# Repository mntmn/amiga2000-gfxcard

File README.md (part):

# MNT VA2000, an Amiga 2000 Graphics Card (Zorro II/III)

_Update January 16th, 2017:_ The MNT VA2000 is now a finished product (credits go to Scarab Hardware for making this happen) that you can buy. I shipped the first batch of 100 cards on christmas 2016 and the second batch is now being made. 

You can still grab one: http://mntshop.bigcartel.com/product/mnt-va2000-amiga-graphics-card-zorro-ii-iii-batch-2-preorder

The latest firmware update and drivers are always available here: http://mntmn.com/va2000/

This repository contains my Kicad schematics and Xilinx ISE/Verilog files for my graphics card project. This is a work in progress, started in October 2015. The first 4 prototypes were assembled in Jan/Feb 2016 and had noise problems, so I started a redesign on Feb 13, 2016.

On Mar 27th, 2016, the redesign worked and I could load a 16 bit 565BGR coded raw image from floppy into the graphics card that displayed a 1280x720p resolution (75mhz pixelclock).

In April 2016, I managed to get Workbench running via a reverse engineered Picasso96 driver.

The working Xilinx project for the new target platform (Scarab miniSpartan 6+) is now in the z2-minispartan folder. The main source file is: https://github.com/mntmn/amiga2000-gfxcard/blob/master/z2-minispartan/z2.v

Contains a modified SDRAM controller (Verilog) and a DVI encoder (VHDL) by Mike Field. See credits and license at the end.

# How I decided to make a graphics card for my Amiga 2000

_TL;DR: I spent my free time over the course of 5 months to make two open source graphics card prototypes for the Amiga 2000. I will make a third, release version; details at the end._

Somewhere in the middle of 2015 I revived my old A500 and acquired again an A1200. Using the A1200, I learned C++ and the basics of web programming in the late 90s. I also used to play many fantastic Amiga games back in the day, made my first music in ProTracker and my first digital graphics in Deluxe Paint. Re-experiencing the old system that was once so ahead of its time again made me curious about Commodore's history – and especially about the later, big and ambitious Amiga models (A3000, A4000…). This coincided with Amiga's 30th anniversary. A lot of new interviews with the original team(s) popped up, including Dave Haynie, who was a main designer of the A2000 and the Zorro III Bus.

I checked eBay for the "big" Amigas I never had, expecting them to be cheap, but found out that these boxes had turned into valuable collector's items. At the same time, A2000s were (and still are) affordable, so I chose to get one and put a 68040 and a SCSI card in it. But the system couldn't realize it's full potential; in the 90s you could already get, for example, a "Picasso" graphics card that could do VGA (and higher) resolutions at 16 or 24bit color depth. Nowadays, these totally outdated cards are rare and sold for ridiculous prices. My A2000 was stuck with 640x256 PAL resolution, 64 colors (ignoring HAM) or headache-inducing interlaced modes. 

Because of my work with microcontrollers, writing an OS for Raspberry Pi (http://interim.mntmn.com/) and my interest in low-level computer architectures in general, I decided in October 2015 in a feat of madness: "I'll just make my own graphics card. How hard can it be?"

It turned out to be a very, very challenging project, but luckily I got much further than expected. On the way, I had to learn how to design a PCB and get it manufactured, how to work with SMD parts, how to program in Verilog and synthesize code for an FPGA, how SDRAM and DVI/HDMI work (or how to get them to do at least something). I also had to find out how to write a driver for the sadly closed/undocumented Picasso96 "retargetable" graphics stack for AmigaOS 3.

The Amiga is probably the last 32-bit personal computer that is fully understood, documented and hackable. Both its hardware and software contain many gems of engineering and design. I hope that one day, we can have a simple but powerful modern computer that is at the same time as hackable and friendly as the Amiga was.

## The "engine": FPGA and SDRAM

As a platform for my first attempt (ultimately a failure) I chose the Papilio Pro development board, which has a Xilinx Spartan 6 FPGA and a few megabytes of SDRAM connected to it. It also has two pin headers that break out some of the general purpose input/output pins of the Spartan. I thought, OK – I could use the RAM to store the image (a framebuffer), and run a loop that goes through all the columns and rows of the picture in the correct speed and just output the bytes from the RAM to R,G and B output lines. I did this before with little Atmel microcontrollers – "bit-banging" a VGA image directly from the CPU – so I knew it was possible. I just didn't know that SDRAM (synchronous dynamic RAM) was a lot more complex to use than the integrated SRAM (static RAM) of common microcontrollers. To access data in a dynamic ram, you have to open banks, rows, precharge, refresh, and take care of startup and access delays:

Source: http://www.alliancememory.com/pdf/dram/256m-as4c16m16s.pdf

Mike Field's open source SDRAM controller written in VHDL and Verilog helped me get the RAM working. I connected an Arduino to the Papilio and used it to send a few address bits and an "on/off" bit to toggle pixels in the framebuffer black or white. This contraption was able to draw basic fonts on my VGA display, and they were successfully kept in the SDRAM. 

The next step was connecting the FPGA+display part to the Amiga 2000.

## Zorro II: Reads and Writes

The original Amiga Hardware Manuals helped me understand the Zorro II bus. It is basically an extension (arbitrated by a bus controller chip) of the pins of the Motorola 68000 CPU. The 68k is extensively studied and documented. I understood that I needed a mechanism that would allow the 68k CPU to write data (pixels) to the graphics card's RAM and another for reading back parts of the screen (for scrolling and moving around things).

So I fired up the open source circuit design tool KiCad and started some schematics. The first task was to define the Zorro port as a component with a whopping 100 pins. Of course I made a lot of little mistakes at first and I had no idea why one would need so many different signals. It turned out that I only needed a subset of the pins to get my job done:

1. Address Bus (A1-A23)
2. Data Bus (D0-D15)
3. Upper and Lower "Data Strobes" (UDS / LDS)
4. READ, /AS, DOE, signals which the Amiga uses to communicate if it wants to read or write, if it presents a valid address and if it expects a device to send data.
5. Power (5V, GND)
6. Autoconf (/CFGIN, /CFGOUT)

Source: https://web.archive.org/web/20140513181907/http://courses.cs.tamu.edu/cpsc462/walker/Slides/68K_Timing_Diagrams.pdf

I figured that I needed to connect most of these signals to the FPGA and then write another loop in Verilog that would interpret the Amiga's bus commands and act on them (store the data given on the bus in the RAM or return stuff from the RAM). 

On the other side of the FPGA, I decided to place an Analog Devices ADV7125 digital to analog converter (DAC) chip that would generate the analog R, G and B channels for the VGA port from the bits coming from the framebuffer.

Source: http://www.analog.com/media/en/technical-documentation/data-sheets/ADV7125.pdf

The next hurdle appeared: The Spartan communicate with modern 3.3V logic levels, but the Amiga used legacy 5V signals. So I needed to put voltage translators (also called level shifters) between the Zorro and the FPGA pins. I decided to split the signals into bundles of 8 and use six 8-bit "auto-direction-sensing" TXS0108 chips.

Source: http://www.ti.com/lit/ds/symlink/txs0108e.pdf

## Mistake: Trying to be too smart

I then realized that the Papilio, the FPGA board I had, didn't have enough I/O pins to connect to the 48 Zorro signals and the 16+2 pins required for the VGA DAC output. Actually, it had a lot less pins. So I made a huge mistake and decided to use two 16-bit port switching chips and "select" on the fly a "window" of the Zorro pins that would be relevant at each state of my bus communication loop; I thought I didn't need to access the data pins at the same time as the address pins. And because the FPGA runs at a much higher frequency than the Zorro bus, I could first read one part of the address, switch one of the switches via a control pin and then quickly read the other part to get the whole address.

After drawing up a few versions of the schematics and collecting the fitting footprints for the components from various GitHub repositories, I imported them into KiCad's PCB design tool and started drawing the actual circuit board. I had no experience doing this, so I worked through tutorials or just looked at how other people were solving their board design problems. Finally, I uploaded the exported "Gerber" files to DirtyPCBs.com, ordered, waited 8 weeks and nothing happened. I made the mistake of choosing the AirMail option, which has no tracking, and the package was lost. After getting no support from DirtyPCB, I chose to try again, this time selecting the DHL option with tracking and finally got my first ever printed circuit boards in the mail around 10 days later! By now, it was the middle of January 2016.

In parallel, I ordered the required chips and parts from Mouser; luckily I had gotten most of the footprints right, except for one logic gate IC that turned out to be a mistake anyway. I got to work and tried to solder my first SMD ICs using my trusted ERSA iron. 

It turned out I had made a number of critical mistakes in designing the boards: all of the voltage translators' OE pins were tied to GND when they should have had 3.3V, so they required manual bending and patching of the OE leg (yellow cables in the picture). I accidentally switched 3.3V and GND pins on the FPGA carrier headers, so I needed to reroute them with wires on the back. Because I misinterpreted the Multiplexer IC's datasheet, I also planned for a negating logic IC on their SEL pins which was totaly wrong. In the end I had to solder bridges instead of placing the 74LS04. 

After fighting through all of these issues and burning through a few boards, I finally got some results. As a first debugging step, I wrote a poor man's logic analyzer in Verilog that would record 640 cycles of all the Zorro Bus signals to FPGA registers (BRAM) and dump them as colorful lines on the VGA screen. This turned out to be a helpful instrument. I wrote a very simple program in 68k assembler for the Amiga that would read – in an endless loop – a word from address $e80000 and write it to $dff180 (a background color register). I made a boot floppy that would run the program, put my card in the A2000, flashed the code and turned everything on.

The first 5 longer, stretched rows in this picture are the signals DOE, READ, /UDS, /AS and E7M (Amiga 7Mhz Clock) sampled at 100 Mhz/Column, so the whole picture displays a time sample of 6400ns (nanoseconds) or 6.4&mu;s (microseconds).

The following lines on the grid represent the Address bits A23-A1 in descending order. A0 does not exist; the 68000 selects an upper, lower or both bytes (word access) using /UDS and /LDS instead.

The address signals have regular little chops in them; this is a nasty side effect of switching the multiplexers. You can also see that address bit A9 is constantly turned on, probably due to a soldering error. At least it's possible to see the 68000's read and subsequent write accesses (the only hole in the READ row, second from the top). Ignoring the broken pins A9 and A17, the READ occurs as expected on address binary 111010000000000000000000 and the WRITE on 0b110111111111000110000000. Due to the constant noise and other random failures, I couldn't reliably get the Amiga to read from my card, but it worked at least sometimes, giving me hope.

After a few nights of trying to fix this very unstable system, I gave up and went back to the drawing board.

## Redesign and Breakthrough

My new strategy was:
1. Make the board much simpler, focus on voltage translation and find a FPGA board with enough IOs
2. Get a decent (de-)soldering station and learn a better SMD soldering technique

I shopped around the web for FPGA boards that combine SDRAM with lots of IO breakouts and found Scarab Hardware's miniSpartan6+, which has a nice small formfactor and includes two HDMI ports, a mini SD card reader and even an audio jack. 

I redrew the schematics to include no more switches, different level shifters with explicit direction inputs (NXP 74LVC8T245), plenty of bypass capacitors and dropped the analog VGA circuit. 

To solve point 2, I ordered a Yihua 853D rework station on Aliexpress and experimented with hot air solder paste soldering (not a success for me, the results were quite messy). I then watched Sparky's super helpful SMD soldering techniques again: https://www.youtube.com/watch?v=z7Tu8NXu5UA

To my surprise, using the "dragging" technique with plenty of flux and a chisel tip (Sparky recommends a "gullwing" tip) at around 270 Celsius yielded the cleanest results I had so far.

Version 2 rewarded me with super clean signals. I used 5 digital outputs of the FPGA and connected them to a VGA monitor for testing, and I could reliably "lock" my Verilog state machine to the Zorro READ cycles. 

I proceeded to write a little 68k assembler program that reads the Amiga's mouse X and Y registers and translates them into an address for the graphics card to write a pixel to. And voila, I had a primitive painting program:

The main problems I had to solve now revolved around tweaking the state machine so that it would arbitrate the single RAM port between fetching pixels for display on the screen – something that is almost constantly happening, only not during blanking periods – and Amiga reads and writes to and from the graphics RAM. I still haven't completely solved this challenge, but I've come far enough for the system to be somewhat usable. The current algorithm works like this:

### Fetching

Shortly before the beginning of each displayed row, start the pixel _fetching_ process. In this state, a line buffer is normally filled with pixels for that line from SDRAM as fast as possible (133 MHz clock).

### Displaying

The VGA/DVI output process reads the pixels to be displayed from this line buffer at the pixel clock frequency (60~75 MHz for a 1280x720 output). This means that the fetching process always needs to be at least as quick or quicker than the displaying process, or there will be glitches (doubling of the last line).

### Host Writes

When the host CPU wants to write to graphics RAM, we don't let it write directly to the SDRAM (because we're probably currently accessing it for fetches). Instead, we save the host's write address and data to a _write queue_. The queue is drained (processed) whenever the line fetching is done for a row and in blanking periods.

I tested the stability of writes by putting the "mon" tool (http://aminet.net/package/dev/moni/mon165) on a floppy together with a raw 16 bit image (rgb565) of a mountain. I loaded this directly into graphics card memory starting at $600000, displaying the first picture ever on my board:

### Host Reads

I found host read timing to be significantly harder to get right, and it's still not perfect. Host reads can't be put in a queue and have to be processed immediately. This interrupts the fetching process; if the host needs to read from a totally different memory location then the display engine is fetching, the SDRAM has to close, refresh and reopen rows, which is a time consuming process. So far, reads from the host cause temporary distortions (glitches) in the display output. I plan to mitigate these problems using either burst mode reads and fast switching and/or inserting CPU wait states via the XRDY signal.

## Picasso96: Writing a Driver for a Closed System

Picasso96 was one of two competing systems (the other being CyberGraphX) integrating graphics cards into the Amiga "Monitor" Device system. P96 also ships an "emulation.library" that patches all system windowing and drawing functions and redirect the legacy bit-planar based output to the new "chunky" pixel formats. After the death of Commodore and the Amiga market, Village Tronic, the authors of P96, disappeared. It's unclear where the sources and internal documentation ended up, and the original developers didn't respond to my emails about it.

I looked at the publically available P96 binaries and documentation and figured that I would need to write a _.card_ file, which is basically a normal Amiga library executable with a different file name extension. From inspecting the binaries and the UAE Picasso96 module, I figured out that my library would have to export a number of function symbols:

- FindCard() to detect if the board is available. I cheated and returned -1 (card found) in d0.
- InitCard(), the most important function, has the job of initializing the board and to fill in a "BoardInfo" structure with details like available pixel color formats, board type, horizontal and vertical maximum resolutions and timings (See: https://github.com/tonioni/WinUAE/blob/master/picasso96.cpp#L1082). This function also stores the addresses of the following callback functions into the BoardInfo structure.

- CalculateBytesPerRow() – Has to return the offset in bytes from one row of pixels to the next. For example: 2048 for a 1024 pixel wide 16-bit display.
- CalculateMemory() – Should remap an address in a1 to another (internal?) address. I just return a1 in d0.
- SetColorArray() – Set the palette for 256 color indexed CLUT mode. I didn't implement this yet.
- ResolvePixelClock() – Supposed to return an index into an array of pixel clocks. Return 0.
- GetPixelClock() – Given an index, return a pixel clock. I just return a fixed number of 60000000.
- SetPanning() – Called when a new P96 screen is opened. In the UAE code, they use it for screen clearing.
- SetSpriteColor() – Just return 0.
- SetDisplay() – enable/disable the display. Just return 0.
- WaitVerticalSync() – Just return 1 or actually sync to the screen refresh process.

Unknown functions: (Stubs that can return 1/0)
- SetSwitch() – Something related to switching between native Amiga and Picasso96 screens.
- SetDAC()
- SetClock()
- GetCompatibleFormats()
- GetVSyncState()
- SetMemoryMode()
- SetWriteMask()
- SetReadPlane()
- SetClearMask()

There is also a number of entrypoints to allow hardware blitting (block copying), rectangle fills and line drawing. I don't implement these yet, but they should speed up working with the card significantly. 

To activate my driver, I had to change the Picasso96 monitor file's "BoardType" tooltype to "VA2000". And indeed, it loaded my VA2000.card without complaining. I then launched the Picasso96Mode application that allows (somewhat erratically) to edit and enable/disable screen modes. To get it to do anything, I copied by trial and error the supplied Picasso96Settings.64 to DEVS:Picasso96Settings and attached the settings to my board that was now showing up in Picasso96Mode's "Board" menu. To my surprise, I could activate the 800x600 mode in "HiColor" and was greeted with a test image and then a somewhat distorted Workbench Screen:

Sprites such as the mouse pointer are emulated in software by Picasso96. In this image you can see some red noisy "turds" from where the mouse pointer was in the frames before – this shows that reading from card memory wasn't working right:

## Fixing the Colors

After playing around with Workbench and several applications, I noticed that somehow I could get only around 64 colors out of the 65535 that should be displayed. This turned out to be a problem of the color format. Picasso96 supports a bunch of 16 bit color modes; for some reasons I had used a "PC" mode (gggrrrrrbbbbbggg) which results in a weird truncation of the color space.

By changing the list of supported color modes in my driver to a non-PC-mode (RGB565), I was able to fix the problem and enjoy "High Color" in 800x600 on my Amiga 2000:

UniView displaying a JPEG (from Hood By Air show):

Obligatory shot of Doom:

## TODO

I will make one more version of the card supporting a reliable manufacturer's FPGA board and the following improvements. If you have the knowledge / tips on how to tackle any of these, feel free to contact me or submit pull requests:

- Fix the remaining noise in writes/reads
- Wait states via XRDY signal: If READ timing cannot be guaranteed or the WRITE queue is full, the card could ask the host CPU to wait by asserting XRDY, avoiding loss of data.
- Switching resolutions and color modes including true color (24 bit)
- Basic hardware block copy and rect filling support
- Digitizing and scandoubling the native amiga video for HDMI output
- Design a proper metal slot plate for connectors

## How can I build or buy a VA2000 board?

I still have to finish the "release" version of the board including the above fixes. I plan to offer preassembled versions and/or construction kits at reasonable prices. If you want to reserve a board, please send me an email to lukas@mntmn.com including "VA2000" in the subject.

All aspects of the project (schematics, PCB, verilog, driver sources) are or will be published as open source under the MIT license, so you are free to produce your own clones of the board.

## Sources, References, Thanks

Special thanks to Martin Åberg for sharing his "GRETA" Amiga 500 expansion sources (https://github.com/endofexclusive/greta). It inspired me to include bus signal synchronizers and helped with AUTOCONF.

Special thanks to Mike Field, his SDRAM and HDMI sources saved me a lot of time:
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
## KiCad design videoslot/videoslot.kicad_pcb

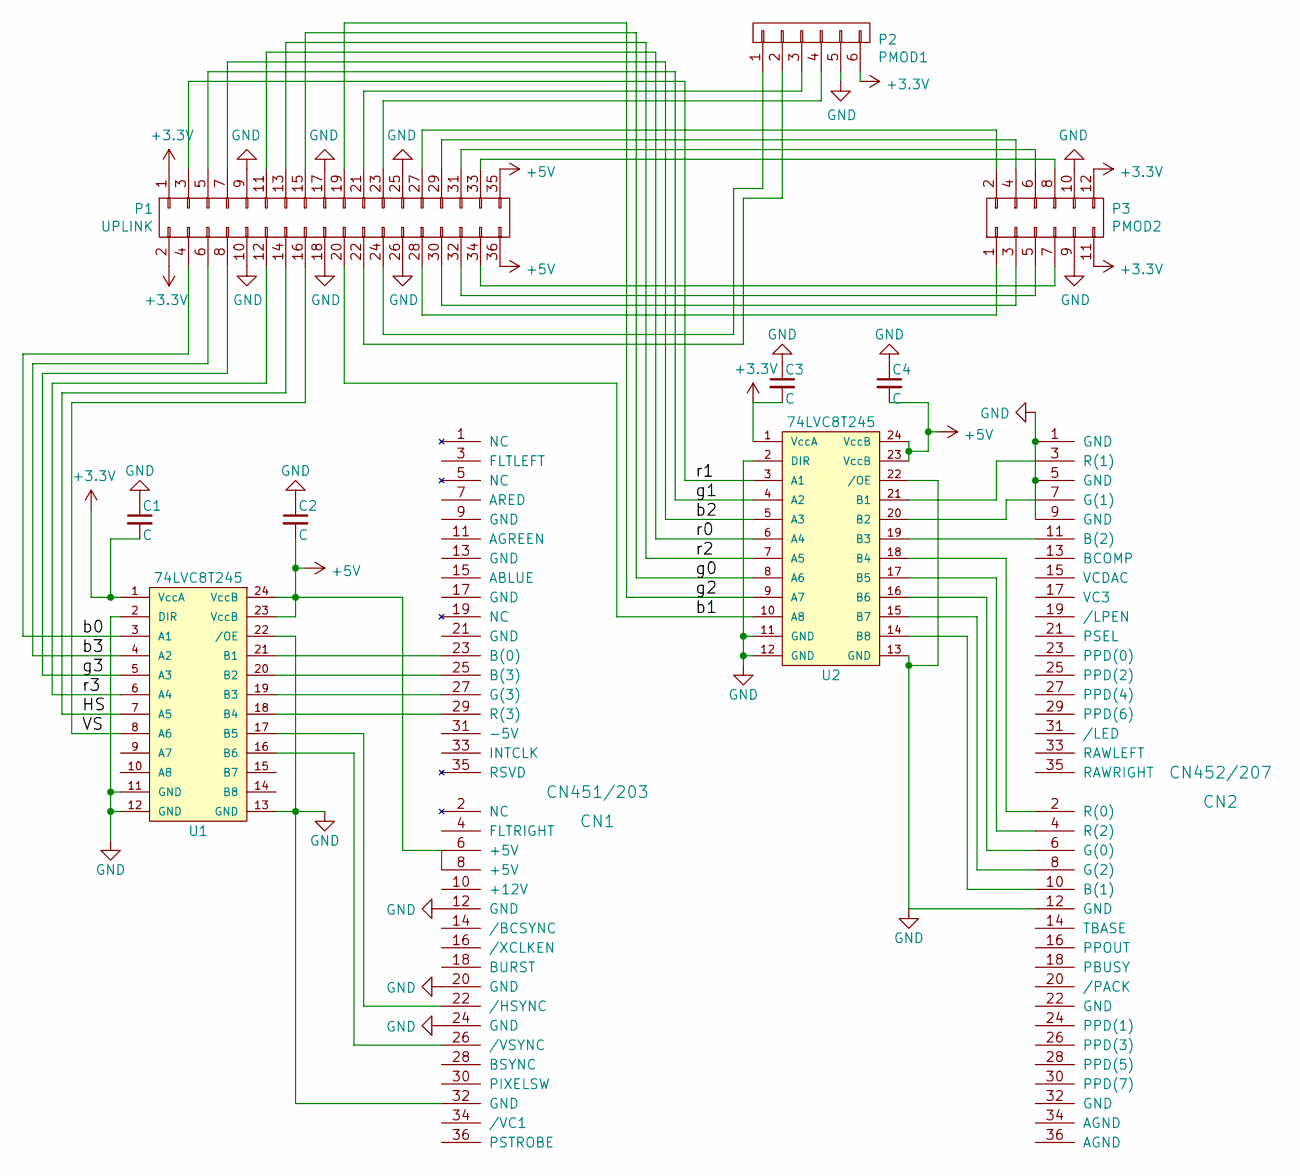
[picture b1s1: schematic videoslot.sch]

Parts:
C1, C2, C3, C4: C; C_0805_HandSoldering
CN1: CN451/203; CN451
CN2: CN452/207; CN452
P1: UPLINK; Pin_Header_Straight_2x18_Pitch2.54mm
P2: PMOD1; Pin_Header_Angled_1x06_Pitch2.54mm
P3: PMOD2; Pin_Header_Angled_2x06_Pitch2.54mm
U1, U2: 74LVC8T245; TSSOP24-44

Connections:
+3V3: C1.2, C3.2, P1.1, P1.2, P2.6, P3.11, P3.12, U1.1 (VccA), U2.1 (VccA)
+5V: C2.2, C4.2, CN1.6 (+5V), CN1.8 (+5V), P1.35, P1.36, U1.23 (VccB), U1.24 (VccB), U2.23 (VccB), U2.24 (VccB)
/HS: P1.14, U1.7 (A5)
/VS: P1.16, U1.8 (A6)
/b0: P1.4, U1.3 (A1)
/b1: P1.20, U2.10 (A8)
/b2: P1.7, U2.5 (A3)
/b3: P1.6, U1.4 (A2)
/g0: P1.15, U2.8 (A6)
/g1: P1.5, U2.4 (A2)
/g2: P1.19, U2.9 (A7)
/g3: P1.8, U1.5 (A3)
/r0: P1.11, U2.6 (A4)
/r1: P1.3, U2.3 (A1)
/r2: P1.13, U2.7 (A5)
/r3: P1.12, U1.6 (A4)
GND: C1.1, C2.1, C3.1, C4.1, CN1.12 (GND), CN1.20 (GND), CN1.24 (GND), CN1.32 (GND), CN2.1 (GND), CN2.5 (GND), CN2.9 (GND), CN2.12 (GND), P1.9, P1.10, P1.17, P1.18, P1.25, P1.26, P2.5, P3.9, P3.10, U1.2 (DIR), U1.11 (GND), U1.12 (GND), U1.13 (GND), U1.22 (/OE), U2.2 (DIR), U2.11 (GND), U2.12 (GND), U2.13 (GND), U2.22 (/OE)
unnamed: CN1.22 (/HSYNC), U1.17 (B5)
unnamed: CN1.23 (B(0)), U1.21 (B1)
unnamed: CN1.25 (B(3)), U1.20 (B2)
unnamed: CN1.26 (/VSYNC), U1.16 (B6)
unnamed: CN1.27 (G(3)), U1.19 (B3)
unnamed: CN1.29 (R(3)), U1.18 (B4)
unnamed: CN2.2 (R(0)), U2.18 (B4)
unnamed: CN2.3 (R(1)), U2.21 (B1)
unnamed: CN2.4 (R(2)), U2.17 (B5)
unnamed: CN2.6 (G(0)), U2.16 (B6)
unnamed: CN2.7 (G(1)), U2.20 (B2)
unnamed: CN2.8 (G(2)), U2.15 (B7)
unnamed: CN2.10 (B(1)), U2.14 (B8)
unnamed: CN2.11 (B(2)), U2.19 (B3)
unnamed: P1.21, P2.3
unnamed: P1.22, P2.2
unnamed: P1.23, P2.4
unnamed: P1.24, P2.1
unnamed: P1.27, P3.2
unnamed: P1.28, P3.1
unnamed: P1.29, P3.4
unnamed: P1.30, P3.3
unnamed: P1.31, P3.6
unnamed: P1.32, P3.5
unnamed: P1.33, P3.8
unnamed: P1.34, P3.7

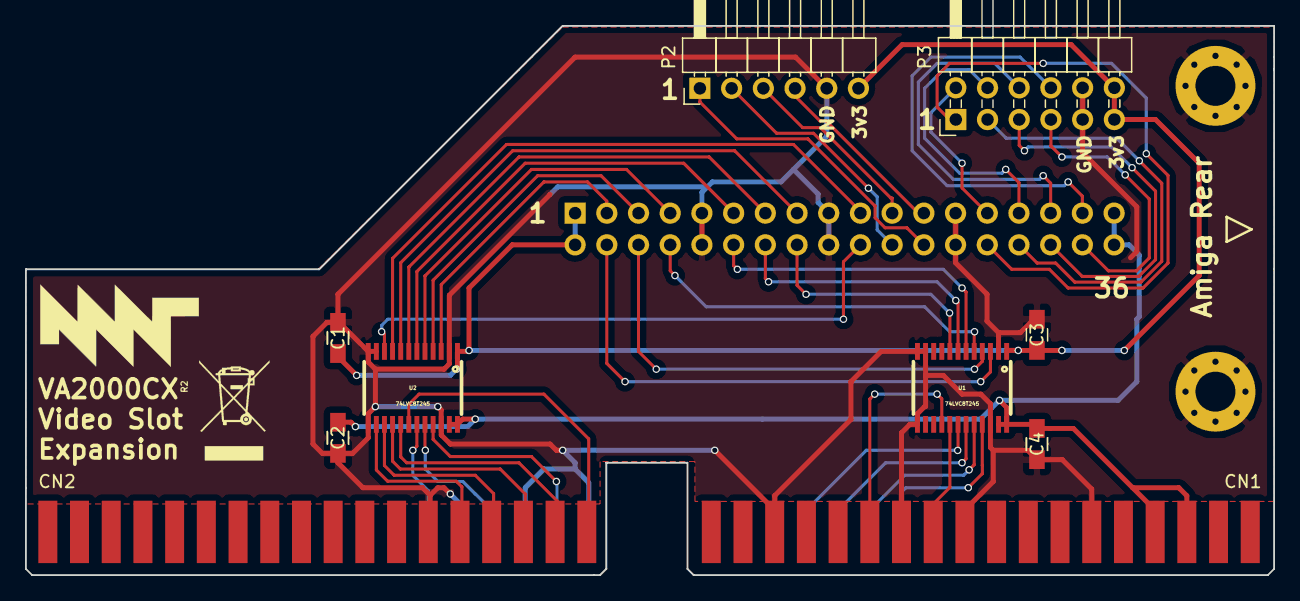
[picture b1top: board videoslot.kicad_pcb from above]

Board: 2 copper layers, 100.0 x 44.0 mm, 11 parts (1 on the bottom side), 43 nets.

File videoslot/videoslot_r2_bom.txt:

U1 U2: SN74LVC8T245PWR 8-Bit Dual-Supply Bus Xcvr
C1 C2 C3 C4: Murata GRM21BR71E104KA01L 0.1uF 0805
P1: Harwin M20-9960645 06 SIL HORIZONTAL PIN HEADER GOLD HT
P2: Harwin M20-9700645 06+06 DIL HORIZONTAL PIN HEADER GOLD HT
P3: Harwin M20-9981845 18+18 DIL VERTICAL PIN HEADER GOLD HT

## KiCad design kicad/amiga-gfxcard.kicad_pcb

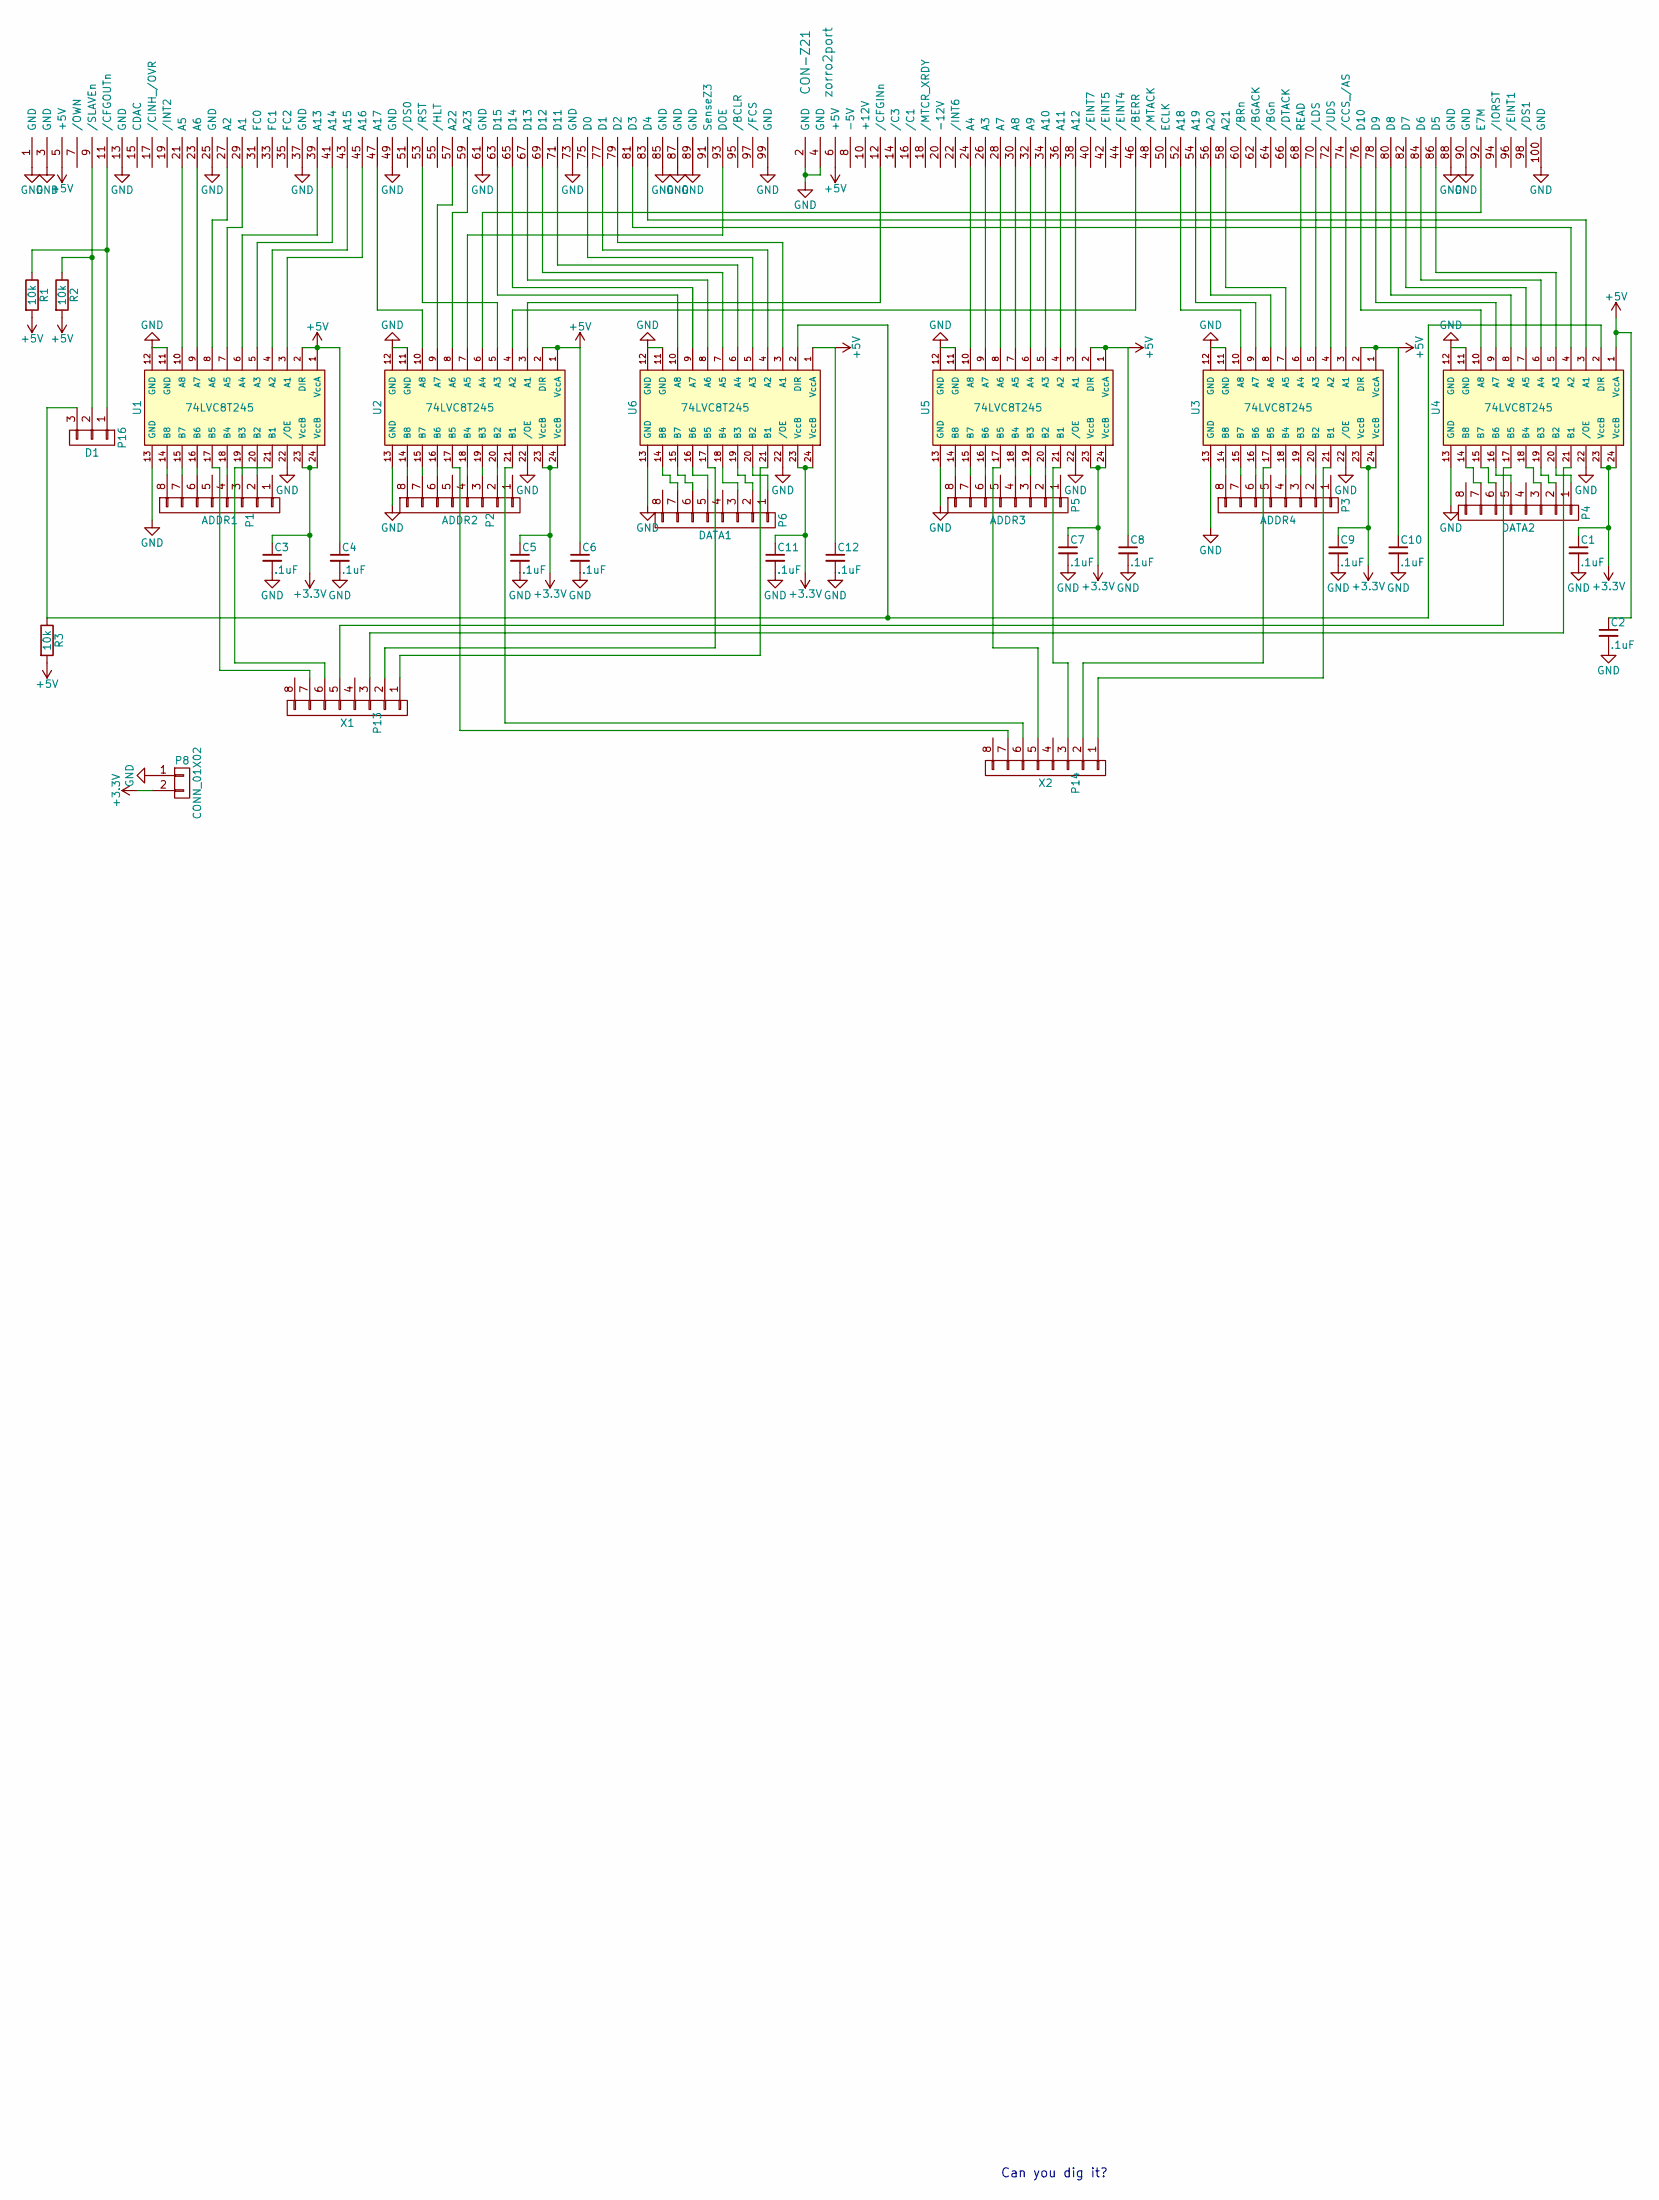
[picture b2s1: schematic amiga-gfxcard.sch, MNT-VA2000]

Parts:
C1, C2, C3, C4, C5, C6, C7, C8, C9, C10, C11, C12: .1uF; C_0805_HandSoldering
CON-Z21: zorro2port; zorro2card
P1: ADDR1; Pin_Header_Straight_1x08
P2: ADDR2; Pin_Header_Straight_1x08
P3: ADDR4; Pin_Header_Straight_1x08
P4: DATA2; Pin_Header_Straight_1x08
P5: ADDR3; Pin_Header_Straight_1x08
P6: DATA1; Pin_Header_Straight_1x08
P8: CONN_01X02; Pin_Header_Straight_1x02
P13: X1; Pin_Header_Straight_1x08
P14: X2; Pin_Header_Straight_1x08
P16: D1; Pin_Header_Straight_1x03
R1, R2, R3: 10k; R_1206_HandSoldering
U1, U2, U3, U4, U5, U6: 74LVC8T245; TSSOP24-44

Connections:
+3V3: C1.1, C3.1, C5.1, C7.1, C9.1, C11.1, P8.2, U1.23 (VccB), U1.24 (VccB), U2.23 (VccB), U2.24 (VccB), U3.23 (VccB), U3.24 (VccB), U4.23 (VccB), U4.24 (VccB), U5.23 (VccB), U5.24 (VccB), U6.23 (VccB), U6.24 (VccB)
+5V: C2.1, C4.1, C6.1, C8.1, C10.1, C12.1, CON-Z21.5 (+5V), CON-Z21.6 (+5V), R1.2, R2.2, R3.2, U1.1 (VccA), U1.2 (DIR), U2.1 (VccA), U2.2 (DIR), U3.1 (VccA), U3.2 (DIR), U4.1 (VccA), U5.1 (VccA), U5.2 (DIR), U6.1 (VccA)
GND: C1.2, C2.2, C3.2, C4.2, C5.2, C6.2, C7.2, C8.2, C9.2, C10.2, C11.2, C12.2, CON-Z21.1 (GND), CON-Z21.2 (GND), CON-Z21.3 (GND), CON-Z21.4 (GND), CON-Z21.13 (GND), CON-Z21.25 (GND), CON-Z21.37 (GND), CON-Z21.49 (GND), CON-Z21.61 (GND), CON-Z21.73 (GND), CON-Z21.85 (GND), CON-Z21.87 (GND), CON-Z21.88 (GND), CON-Z21.89 (GND), CON-Z21.90 (GND), CON-Z21.99 (GND), CON-Z21.100 (GND), P8.1, U1.11 (GND), U1.12 (GND), U1.13 (GND), U1.22 (/OE), U2.11 (GND), U2.12 (GND), U2.13 (GND), U2.22 (/OE), U3.11 (GND), U3.12 (GND), U3.13 (GND), U3.22 (/OE), U4.11 (GND), U4.12 (GND), U4.13 (GND), U4.22 (/OE), U5.11 (GND), U5.12 (GND), U5.13 (GND), U5.22 (/OE), U6.11 (GND), U6.12 (GND), U6.13 (GND), U6.22 (/OE)
unnamed: CON-Z21.9 (/SLAVEn), P16.2, R2.1
unnamed: CON-Z21.11 (/CFGOUTn), P16.1, R1.1
unnamed: CON-Z21.12 (/CFGINn), U2.3 (A1)
unnamed: CON-Z21.21 (A5), U1.10 (A8)
unnamed: CON-Z21.23 (A6), U1.9 (A7)
unnamed: CON-Z21.24 (A4), U5.10 (A8)
unnamed: CON-Z21.26 (A3), U5.9 (A7)
unnamed: CON-Z21.27 (A2), U1.8 (A6)
unnamed: CON-Z21.28 (A7), U5.8 (A6)
unnamed: CON-Z21.29 (A1), U1.7 (A5)
unnamed: CON-Z21.30 (A8), U5.7 (A5)
unnamed: CON-Z21.32 (A9), U5.6 (A4)
unnamed: CON-Z21.34 (A10), U5.5 (A3)
unnamed: CON-Z21.36 (A11), U5.4 (A2)
unnamed: CON-Z21.38 (A12), U5.3 (A1)
unnamed: CON-Z21.39 (A13), U1.6 (A4)
unnamed: CON-Z21.41 (A14), U1.5 (A3)
unnamed: CON-Z21.43 (A15), U1.4 (A2)
unnamed: CON-Z21.45 (A16), U1.3 (A1)
unnamed: CON-Z21.46 (/BERR), U2.4 (A2)
unnamed: CON-Z21.47 (A17), U2.10 (A8)
unnamed: CON-Z21.52 (A18), U3.10 (A8)
unnamed: CON-Z21.53 (/RST), U2.5 (A3)
unnamed: CON-Z21.54 (A19), U3.9 (A7)
unnamed: CON-Z21.56 (A20), U3.8 (A6)
unnamed: CON-Z21.57 (A22), U2.9 (A7)
unnamed: CON-Z21.58 (A21), U3.7 (A5)
unnamed: CON-Z21.59 (A23), U2.8 (A6)
unnamed: CON-Z21.63 (D15), U6.10 (A8)
unnamed: CON-Z21.65 (D14), U6.9 (A7)
unnamed: CON-Z21.67 (D13), U6.8 (A6)
unnamed: CON-Z21.68 (READ), U3.6 (A4)
unnamed: CON-Z21.69 (D12), U6.7 (A5)
unnamed: CON-Z21.70 (/LDS), U3.5 (A3)
unnamed: CON-Z21.71 (D11), U6.6 (A4)
unnamed: CON-Z21.72 (/UDS), U3.4 (A2)
unnamed: CON-Z21.74 (/CCS_/AS), U3.3 (A1)
unnamed: CON-Z21.75 (D0), U6.5 (A3)
unnamed: CON-Z21.76 (D10), U4.10 (A8)
unnamed: CON-Z21.77 (D1), U6.4 (A2)
unnamed: CON-Z21.78 (D9), U4.9 (A7)
unnamed: CON-Z21.79 (D2), U6.3 (A1)
unnamed: CON-Z21.80 (D8), U4.8 (A6)
unnamed: CON-Z21.81 (D3), U4.4 (A2)
unnamed: CON-Z21.82 (D7), U4.7 (A5)
unnamed: CON-Z21.83 (D4), U4.3 (A1)
unnamed: CON-Z21.84 (D6), U4.6 (A4)
unnamed: CON-Z21.86 (D5), U4.5 (A3)
unnamed: CON-Z21.92 (E7M), U2.6 (A4)
unnamed: CON-Z21.93 (DOE), U2.7 (A5)
unnamed: P1.2, U1.20 (B2)
unnamed: P1.3, U1.19 (B3)
unnamed: P1.4, U1.18 (B4)
unnamed: P1.6, U1.16 (B6)
unnamed: P1.7, U1.15 (B7)
unnamed: P1.8, U1.14 (B8)
unnamed: P2.2, U2.20 (B2)
unnamed: P2.3, U2.19 (B3)
unnamed: P2.4, U2.18 (B4)
unnamed: P2.6, U2.16 (B6)
unnamed: P2.7, U2.15 (B7)
unnamed: P2.8, U2.14 (B8)
unnamed: P3.2, U3.20 (B2)
unnamed: P3.3, U3.19 (B3)
unnamed: P3.4, U3.18 (B4)
unnamed: P3.6, U3.16 (B6)
unnamed: P3.7, U3.15 (B7)
unnamed: P3.8, U3.14 (B8)
unnamed: P4.1, U4.20 (B2)
unnamed: P4.2, U4.19 (B3)
unnamed: P4.3, U4.18 (B4)
unnamed: P4.5, U4.16 (B6)
unnamed: P4.6, U4.15 (B7)
unnamed: P4.7, U4.14 (B8)
unnamed: P5.2, U5.20 (B2)
unnamed: P5.3, U5.19 (B3)
unnamed: P5.4, U5.18 (B4)
unnamed: P5.6, U5.16 (B6)
unnamed: P5.7, U5.15 (B7)
unnamed: P5.8, U5.14 (B8)
unnamed: P6.1, U6.20 (B2)
unnamed: P6.2, U6.19 (B3)
unnamed: P6.3, U6.18 (B4)
unnamed: P6.5, U6.16 (B6)
unnamed: P6.6, U6.15 (B7)
unnamed: P6.7, U6.14 (B8)
unnamed: P13.1, U6.21 (B1)
unnamed: P13.2, U6.17 (B5)
unnamed: P13.3, U4.21 (B1)
unnamed: P13.5, U4.17 (B5)
unnamed: P13.6, U1.21 (B1)
unnamed: P13.7, U1.17 (B5)
unnamed: P14.1, U3.21 (B1)
unnamed: P14.2, U3.17 (B5)
unnamed: P14.3, U5.21 (B1)
unnamed: P14.5, U5.17 (B5)
unnamed: P14.6, U2.21 (B1)
unnamed: P14.7, U2.17 (B5)
unnamed: P16.3, R3.1, U4.2 (DIR), U6.2 (DIR)

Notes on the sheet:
Can you dig it?

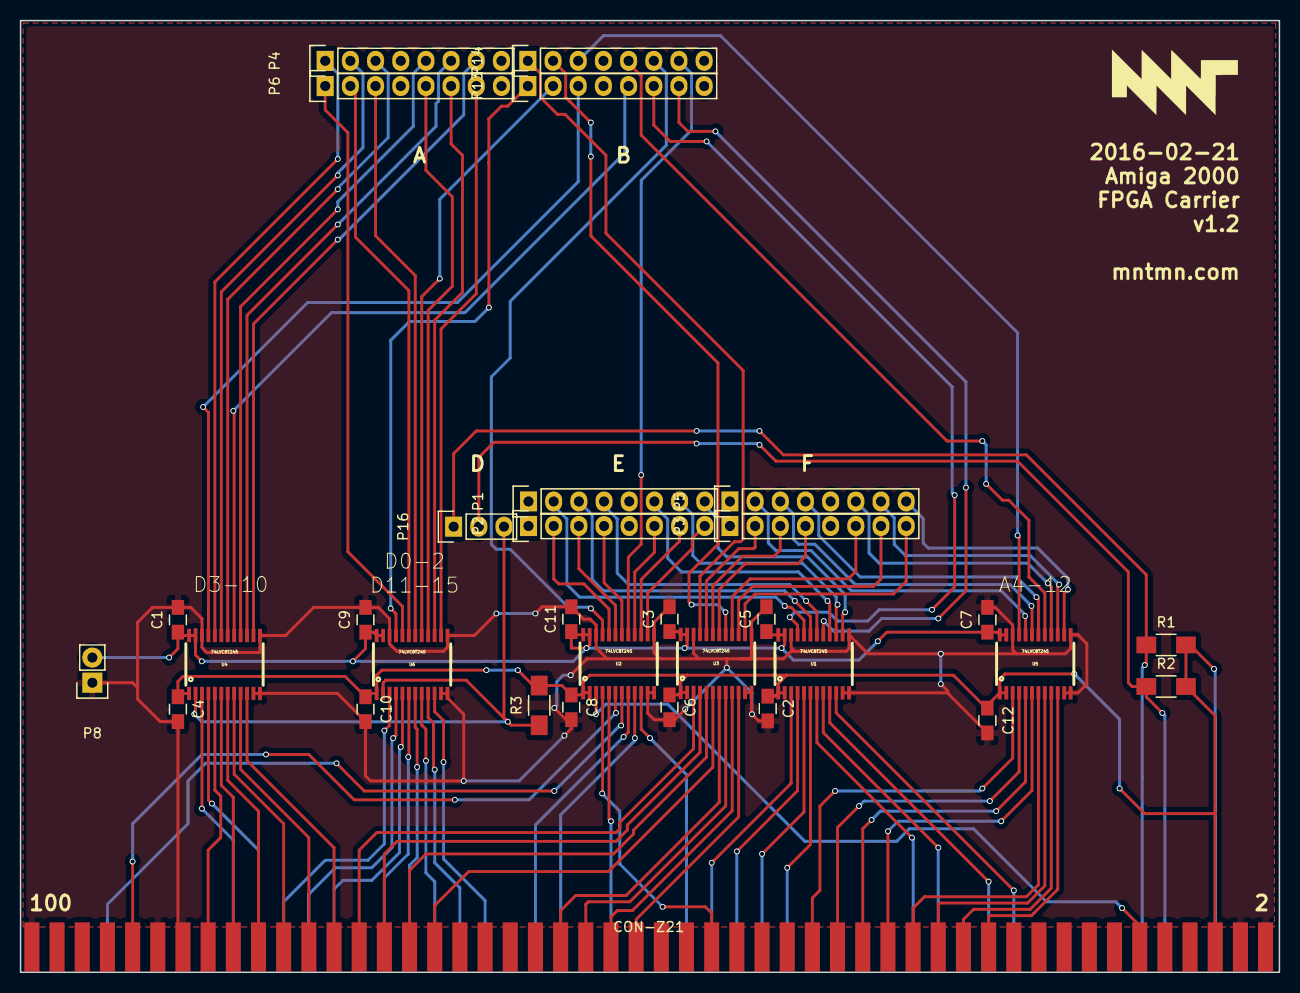
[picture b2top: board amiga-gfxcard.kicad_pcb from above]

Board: 2 copper layers, 127.0 x 96.0 mm, 32 parts (0 on the bottom side), 102 nets.

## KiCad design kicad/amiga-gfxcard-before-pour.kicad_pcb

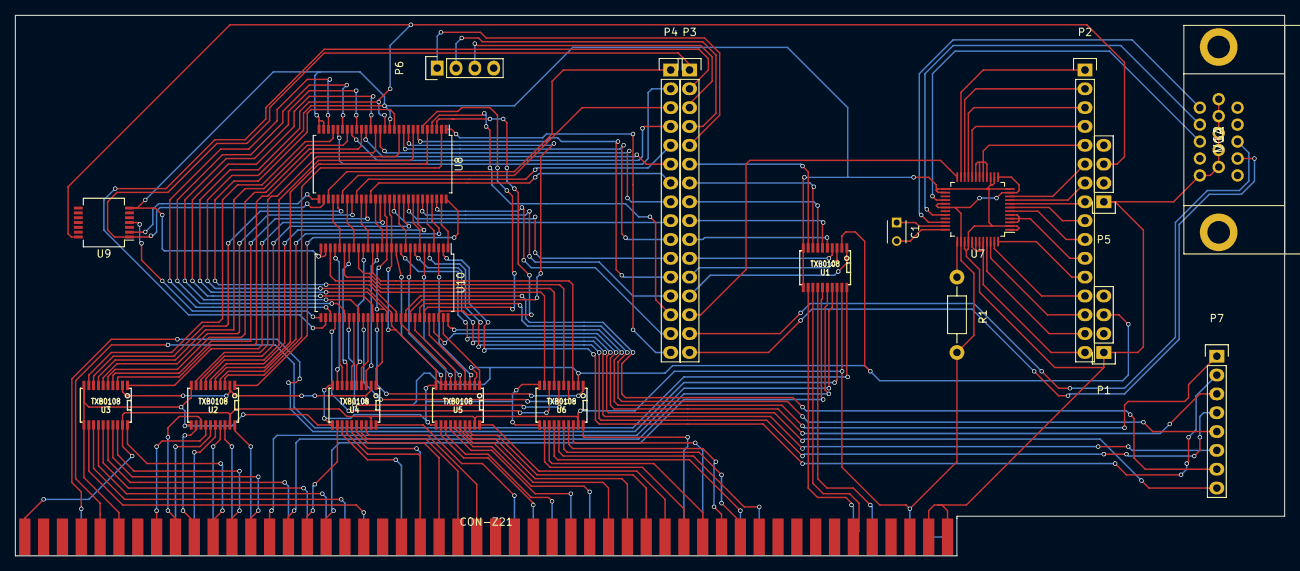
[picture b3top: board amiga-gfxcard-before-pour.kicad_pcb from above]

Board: 2 copper layers, 171.2 x 72.9 mm, 21 parts (0 on the bottom side), 172 nets.

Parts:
C1: 0.1uF; C_Disc_D3_P2.5
CON-Z21: zorro2port; zorro2card
P1, P5, P6: CONN_01X04; Pin_Header_Straight_1x04
P2, P3, P4: CONN_01X16; Pin_Header_Straight_1x16
P7: CONN_01X08; Pin_Header_Straight_1x08
R1: 82k; Resistor_Horizontal_RM10mm
U1, U2, U3, U4, U5, U6: TXB0108; TSSOP20_PW
U7: ADV7125-lqfp48; LQFP-48_7x7mm_Pitch0.5mm
U8, U10: SN74CBT16233; SSOP-56_7.5x18.5mm_Pitch0.635mm
U9: 74LS04; SSOP-14_5.3x6.2mm_Pitch0.65mm
U12: VGA; HD15_B-HD15F

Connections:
//AS: CON-Z21.74, U1.17
//LDS: CON-Z21.70, U4.12
//UDS: CON-Z21.72, U1.16
/A1: CON-Z21.29, U6.20
/A8: CON-Z21.30, U6.12
/A9: CON-Z21.32, U5.20
/A16: CON-Z21.45, U5.12
/A17: CON-Z21.47, U4.20
/A23: CON-Z21.59, U4.13
/D0: CON-Z21.75, U2.20
/D7: CON-Z21.82, U2.12
/D8: CON-Z21.80, U3.20
/D15: CON-Z21.63, U3.12
GND: CON-Z21.1, CON-Z21.2, CON-Z21.3, CON-Z21.4, CON-Z21.90, P1.1, P5.1, U1.10, U1.11, U2.10, U2.11, U3.10, U3.11, U4.10, U4.11, U5.10, U5.11, U6.10, U6.11, U7.1, U7.2, U7.12, U7.14, U7.15, U7.25, U7.26, U7.39, U7.40, U8.13, U8.27, U8.28, U8.44, U9.7, U10.13, U10.27, U10.28, U10.44, U12.5, U12.6, U12.7, U12.8, U12.9, U12.10
unnamed: C1.1, U7.35
unnamed: C1.2, U7.36
unnamed: CON-Z21.9, U1.14
unnamed: CON-Z21.11, U1.12
unnamed: CON-Z21.12, U1.13
unnamed: CON-Z21.21, U6.15
unnamed: CON-Z21.23, U6.14
unnamed: CON-Z21.24, U6.16
unnamed: CON-Z21.26, U6.17
unnamed: CON-Z21.27, U6.18
unnamed: CON-Z21.28, U6.13
unnamed: CON-Z21.34, U5.18
unnamed: CON-Z21.36, U5.17
unnamed: CON-Z21.38, U5.16
unnamed: CON-Z21.39, U5.15
unnamed: CON-Z21.41, U5.14
unnamed: CON-Z21.43, U5.13
unnamed: CON-Z21.52, U4.18
unnamed: CON-Z21.54, U4.17
unnamed: CON-Z21.56, U4.16
unnamed: CON-Z21.57, U4.15
unnamed: CON-Z21.58, U4.14
unnamed: CON-Z21.65, U3.13
unnamed: CON-Z21.67, U3.14
unnamed: CON-Z21.68, U1.15
unnamed: CON-Z21.69, U3.15
unnamed: CON-Z21.71, U3.16
unnamed: CON-Z21.76, U3.17
unnamed: CON-Z21.77, U2.18
unnamed: CON-Z21.78, U3.18
unnamed: CON-Z21.79, U2.17
unnamed: CON-Z21.81, U2.16
unnamed: CON-Z21.83, U2.15
unnamed: CON-Z21.84, U2.13
unnamed: CON-Z21.86, U2.14
unnamed: CON-Z21.92, U1.20
unnamed: CON-Z21.93, U1.18
unnamed: CON-Z21.5, CON-Z21.6, CON-Z21.100, R1.2, U1.19, U2.19, U3.19, U4.19, U5.19, U6.19, U7.11, U7.13, U7.29, U7.30, U7.38
unnamed: P1.3, U1.2, U2.2, U3.2, U4.2, U5.2, U6.2
unnamed: P2.1, U7.23
unnamed: P2.2, U7.22
unnamed: P2.3, U7.21
unnamed: P2.4, U7.20
unnamed: P2.5, U7.16, U7.17, U7.18, U7.19
unnamed: P2.6, U7.10
unnamed: P2.7, U7.9
unnamed: P2.8, U7.8
unnamed: P2.9, U7.7
unnamed: P2.10, U7.6
unnamed: P2.11, U7.3, U7.4, U7.5
unnamed: P2.12, U7.48
unnamed: P2.13, U7.47
unnamed: P2.14, U7.46
unnamed: P2.15, U7.45
unnamed: P2.16, U7.41, U7.42, U7.43, U7.44
unnamed: P3.1, U8.30, U9.1
unnamed: P3.2, U10.30
unnamed: P3.3, P6.3
unnamed: P3.4, P6.2
unnamed: P3.5, P6.1
unnamed: P3.6, U1.9
unnamed: P3.7, U1.8
unnamed: P3.8, U1.7
unnamed: P3.9, U1.6
unnamed: P3.10, U1.5
unnamed: P3.11, U1.4
unnamed: P3.12, U1.3
unnamed: P3.13, U1.1
unnamed: P3.14, U7.24
unnamed: P3.15, U12.13
unnamed: P3.16, U12.14
unnamed: P4.1, U8.31
unnamed: P4.2, U8.24
unnamed: P4.3, U8.34
unnamed: P4.4, U8.21
unnamed: P4.5, U8.37
unnamed: P4.6, U8.18
unnamed: P4.7, U8.40
unnamed: P4.8, U8.15
unnamed: P4.9, U8.45
unnamed: P4.10, U8.10
unnamed: P4.11, U8.48
unnamed: P4.12, U8.7
unnamed: P4.13, U8.51
unnamed: P4.14, U8.4
unnamed: P4.15, U8.54
unnamed: P4.16, U8.1
unnamed: P5.3, U8.14, U8.43, U10.14, U10.43
unnamed: P7.1, U10.56
unnamed: P7.2, U10.2
unnamed: P7.3, U10.53
unnamed: P7.4, U10.5
unnamed: P7.5, U10.50
unnamed: P7.6, U10.8
unnamed: P7.7, U10.47
unnamed: P7.8, U10.11
unnamed: R1.1, U7.37
unnamed: U2.1, U8.56
unnamed: U2.3, U8.2
unnamed: U2.4, U8.53
unnamed: U2.5, U8.5
unnamed: U2.6, U8.50
unnamed: U2.7, U8.8
unnamed: U2.8, U8.47
unnamed: U2.9, U8.11
unnamed: U3.1, U8.42
unnamed: U3.3, U8.16
unnamed: U3.4, U8.39
unnamed: U3.5, U8.19
unnamed: U3.6, U8.36
unnamed: U3.7, U8.22
unnamed: U3.8, U8.33
unnamed: U3.9, U8.25
unnamed: U8.29, U9.2
unnamed: U8.55, U10.1
unnamed: U5.3, U10.3
unnamed: U8.52, U10.4
unnamed: U5.5, U10.6
unnamed: U8.49, U10.7
unnamed: U5.7, U10.9
unnamed: U8.46, U10.10
unnamed: U5.9, U10.12
unnamed: U8.41, U10.15
unnamed: U4.3, U10.16
unnamed: U6.3, U10.17
unnamed: U8.38, U10.18
unnamed: U4.5, U10.19
unnamed: U6.5, U10.20
unnamed: U8.35, U10.21
unnamed: U4.7, U10.22
unnamed: U6.7, U10.23
unnamed: U8.32, U10.24
unnamed: U4.9, U10.25
unnamed: U6.9, U10.26
unnamed: U9.4, U10.29
unnamed: U8.26, U10.31
unnamed: U6.8, U10.32
unnamed: U4.8, U10.33
unnamed: U8.23, U10.34
unnamed: U6.6, U10.35
unnamed: U4.6, U10.36
unnamed: U8.20, U10.37
unnamed: U6.4, U10.38
unnamed: U4.4, U10.39
unnamed: U8.17, U10.40
unnamed: U6.1, U10.41
unnamed: U4.1, U10.42
unnamed: U8.12, U10.45
unnamed: U5.8, U10.46
unnamed: U8.9, U10.48
unnamed: U5.6, U10.49
unnamed: U8.6, U10.51
unnamed: U5.4, U10.52
unnamed: U8.3, U10.54
unnamed: U5.1, U10.55
unnamed: U7.34, U12.1
unnamed: U7.32, U12.2
unnamed: U7.28, U12.3

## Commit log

2016-02-13 initial
2016-02-17 WIP of simpler redesign for miniSpartan 6+
2016-02-18 WIP new PCB
2016-02-18 redo of mk2 board finished
2016-02-21 board v1.2 finished
2016-03-27 Version 2, new board, minispartan 6+, working DVI/HDMI output
2016-04-01 quite well working version with 1024x720 mapped to 720p dvi and read/write support
2016-04-06 cleanup, new timing model
2016-04-07 add testbench; reduce sdram controller to 16bit (no burst)
2016-04-08 hopefully good read/write/fetch machine; simulated
2016-04-09 quite stable writes; fix weird 16bit 'pc' color interpretation
2016-04-10 first usable version!
2016-04-13 simulated full-page burst for fetching
2016-04-13 only serve first word of host read burst
2016-04-13 screen_w
2016-04-13 new r5g6b5 colormode
2016-04-14 WIP docs
2016-04-16 article WIP without pics
2016-04-16 WIP article
2016-04-16 Docs WIP
2016-04-16 crop tina
2016-04-16 consolidate readme
2016-04-16 more readme cleanup
2016-04-16 readme tweaks, added missing sources
2016-04-17 Update README.md
    Fixed typo
2016-04-18 Update README.md
    Remove errand 'g'
2016-04-20 WIP/tests
2016-04-24 disable sdram refresh; less glitches
2016-04-24 read-to-fetch timer test
2016-04-26 not perfect, but much better.
2016-05-05 xrdy mechanism; display stable; minimal wrong pixels
2016-05-06 optimal de-glitching parameters
2016-05-07 good version for 1280x720p 16bit
2016-05-14 working autoconfig(tm), experimental video slot grabber, experimental sd/spi interface
2016-05-15 first partly working version of SD card driver
2016-05-15 a good bitfile (v20150516)
2016-05-21 WIP clean-room card driver headers compatible with a popular RTG library
2016-05-21 Scarab are totally back (there server was down)
2016-05-22 rtg driver WIP
2016-05-22 before trying different sdr controller
2016-05-22 WIP cleaner high-level structure; sdram controller debugging
2016-05-23 WIP read/write mix debugging
2016-05-24 debug uart; fix read/write addr noise
2016-05-25 stable read/writes, no more ffff noise; added missing uart source
2016-05-26 first working gfx driver
2016-05-28 before registerizing
2016-05-28 WIP with blitter and working C gfx driver
2016-06-04 first promising burst version
2016-06-04 2 faulty rows to go
2016-06-07 almost glitch-free
2016-06-19 first working SD card driver; minimized flickering when blitter is copying
2016-06-28 hardware sprite support
2016-06-28 stability tweaks to SD card device
2016-06-28 don't ignore .bit files
2016-07-10 add missing UCF file
2016-07-10 fix gfx driver board flags
2016-08-14 WIP initial Z3 code
2016-08-21 full z3 writes; reads; register writes
2016-08-27 WIP working autoconfig memory allocation
2016-08-29 WIP before blitter rewrite
2016-08-29 copy timing and scaling problems solved
2016-09-01 Z2/Z3 sensing and support for both generations WIP
2016-09-25 glitchless at 145/72.5mhz
2016-09-25 scale fix
2016-10-30 SD_BASE for sd card driver
2016-11-28 fix wip
2016-11-28 fix blitter driver for renderinfo offsets etc
2016-12-11 beta release WIP. 32bit, fix some timing problems, introduce custom refresh, fix sd card drivers, sd card CRC, custom resolutions, fix z3 register read model
2016-12-12 WIP timing
2016-12-13 fix SD card driver; much better timing
2016-12-13 RC1 bitfile
2016-12-14 a2000 tweaks (fixed read turd bug), working refresh
2016-12-14 reactivate CRC check on read
2016-12-14 RC2 release bitfile
2016-12-21 release 1.0 binary files
2016-12-22 fix corrupted Picasso96Settings file; init refresh timer in driver
2017-01-02 WIP cfgin/cfgout sequencing; fix possible deadlock when switching resolutions; some blitter optimization; revision number
2017-01-02 WIP send syncs on all 3 channels until we figure out the right one; improves monitor compatibility
2017-01-05 stable state snapshot
2017-01-05 firmware 1.3rc1; fixes lockups and write errors switching between pixel clocks
2017-01-06 1.3rc2 adds 3rd pixelclock for 1280x1024
2017-01-13 debugged snapshot
2017-01-14 snapshot
2017-01-14 switch from xrdy to ovr/dtack mechanism; fix last glitches with default_data = ffff
2017-01-14 before z3 tests
2017-01-15 snapshot Z3 stable
2017-01-15 green timing with 32b + z2
2017-01-15 RC snapshot
2017-01-15 timing closure & everything looks good
2017-01-15 firmare 1.3 release
2017-01-15 README bump
2017-01-15 va2000 production pic
2017-01-17 amend some changes: dvid sync channel swapped; sd main clock set to 50mhz; disabled some TIGs
2017-01-29 stable point after lots of 3000/030 z3 debugging. adds DOE gate, fixes some write/read race conditions
2017-01-29 1.4 rc1
2017-02-08 added schematics of release board
2017-02-09 scandoubler working snapshot
2017-02-11 capture mode snapshot #2
2017-02-12 introduce 2-word burst in ram controller; accidentally fix long-standing bug; stable hi-res capture
2017-02-14 reactivate blitter, capture mode, integrate matzes palette fix
2017-02-14 added matze's clockfix and corrected palette fix
2017-02-22 gfx driver cleanup & refactoring
2017-02-22 capture pins
2017-02-22 separate blitter pitch + colormode
2017-03-04 some refactoring and blitter fixes for release 1.4
2017-03-04 clean up timing constraints in UCF; false path muxed vga clocks
2017-03-04 release 1.4; sync all vga signals across clocks; refactor some blitter code into more states; clear memory on reset; no more blue screen; sync some sd out signals; no more clock switching crashes
2017-03-05 videoslot expansion protoype
2017-03-12 color cycling test for scarab
2017-03-12 VA2000CX corrections for PCB batch 1
2017-04-26 first boot code experiments
2017-05-25 WIP 1.5b firmware, gfx drivers; mntmode, va2000cx initial commits
2017-07-24 1.6.1 firmware, drivers, va2000cx tool; mainly videocap improvements, new regs
2017-08-15 first working SD autoboot version, fw1.7 RC1
2017-08-15 untabify bootrom asm files
2017-09-18 fw1.7.1 better blitter write handling; bigger blitter regs; dtack latch for timing closure (might have caused incompats?)
2017-09-26 Release 1.7.2 FW, gfx & sd driver
2017-09-26 revert card/chip type constants
2017-09-29 experimental vbcc version of mntgfx.card
2017-10-02 snapshot of 1.8 fw with deinterlacer
2017-10-04 first OK prototype of linear framebuffer
2017-10-08 checkpoint
2017-10-10 most modes and capture working correctly again
2017-10-10 register, blitter, refresh restructuring, 32bit scaler fixed
2017-10-11 1.8.2 beta 1 stable; slight pixel errors due to refresh
2017-10-11 beta1 drivers for 1.8.2, new framebuffer and blitter model
2017-10-26 firmware and gfx driver source for 1.8.3, updated va2000cx tool
2018-01-31 some naming cleanup for va2000 xilinx fpga project folders/files, 1.8.4 WIP
2018-05-13 OK working dev snapshot of 1.8.5
2018-05-13 relax row buffer fetch done logic
2018-05-14 8.1.5RC1 verilog snapshot; 20% copy blitter perf boost; monochrome planar mode
2018-05-14 1.8.5 driver, missing .xise update
2018-07-16 first workable cleaned up sdram controller; write + blit speedups
2018-07-18 working 32bit color mode and clean video grabber; only smaller glitches left
2018-07-19 snapshot of glitch-free block copy
2018-07-19 1.9.0 beta 1 release for zorro 3 (z2 disabled)
2018-08-03 1.9.0 release
2018-08-24 add missing va2000cx components
2018-08-24 va2000cx: added duplicates of all needed symbols
2018-08-24 15 bit support in mntgfx and some fixes
2018-08-24 cli build script
2019-03-15 initial driver code for ZZ9000
2019-03-20 busy flag gating for register writes
2019-03-20 add missing header
2019-03-25 videoslot (cx) cache and rescue lib
2019-03-25 cx r2 BOM
2019-03-26 WIP introduce 720x576@50hz mode for native passthrough
2019-03-28 WIP some vsync cleanups
2019-04-04 WIP network driver
2021-11-08 Update README.md
    https://forum.kicad.info/t/warning-avoid-all-links-to-kicad-pcb-org-use-kicad-org/31521
2021-11-08 Update README.html
    https://forum.kicad.info/t/warning-avoid-all-links-to-kicad-pcb-org-use-kicad-org/31521
2022-12-15 PDF.txt
    pdf sources

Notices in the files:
README.md:
Copyright / License:
(C)2016 Lukas F. Hartmann (@mntmn) / MNT Media and Technology UG.
http://mntmn.com
https://twitter.com/mntmn
Permission is hereby granted, free of charge, to any person obtaining a copy of this software and associated documentation files (the "Software"), to deal in the Software without restriction, including without limitation the rights to use, copy, modify, merge, publish, distribute, sublicense, and/or sell copies of the Software, and to permit persons to whom the Software is furnished to do so, subject to the following conditions: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
